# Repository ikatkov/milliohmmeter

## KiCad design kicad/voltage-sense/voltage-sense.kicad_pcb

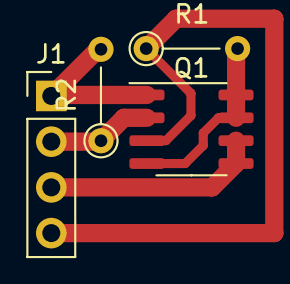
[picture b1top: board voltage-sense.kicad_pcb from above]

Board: 4 copper layers, 4 parts (0 on the bottom side), 5 nets.

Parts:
J1: Conn_01x04_Male; PinHeader_1x04_P2.54mm_Vertical
Q1: Si4532DY; SOIC-8_3.9x4.9mm_P1.27mm
R1: 1M; R_Axial_DIN0204_L3.6mm_D1.6mm_P5.08mm_Vertical
R2: 10k; R_Axial_DIN0204_L3.6mm_D1.6mm_P5.08mm_Vertical

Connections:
ADC: J1.3, Q1.5, Q1.6
BATT: J1.4, Q1.3, R1.1
GND: J1.1, Q1.1, R2.2
unnamed: Q1.4, Q1.7, Q1.8, R1.2
VCC: J1.2, Q1.2, R2.1

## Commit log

2021-11-22 cleanup
2021-12-05 add battery management
2021-12-06 auto turn off
2021-12-06 minor fixes
